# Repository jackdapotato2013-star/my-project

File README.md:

# my-project
A new project with 4 files

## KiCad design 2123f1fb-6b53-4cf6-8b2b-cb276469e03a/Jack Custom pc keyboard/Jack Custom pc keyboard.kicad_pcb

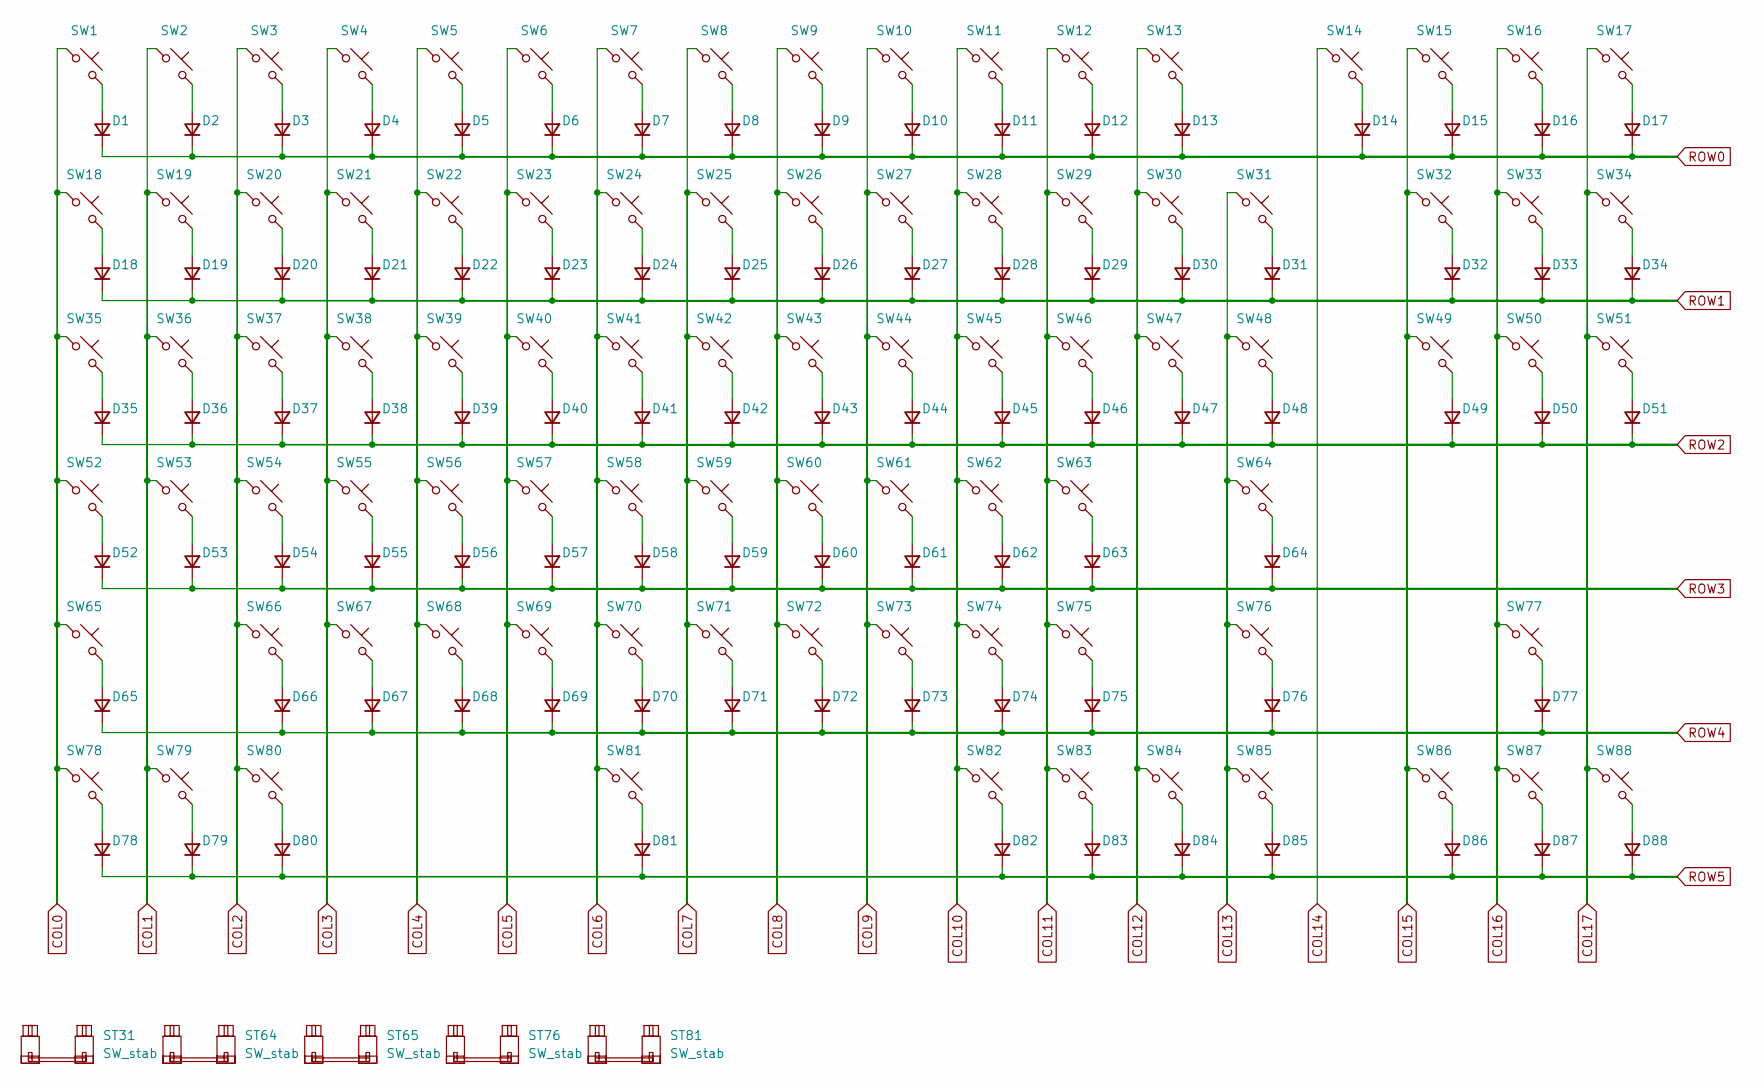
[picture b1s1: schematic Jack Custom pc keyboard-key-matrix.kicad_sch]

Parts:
D1, D2, D3, D4, D5, D6, D7, D8, D9, D10, D11, D12, D13, D14, D15, D16, D17, D18, D19, D20, D21, D22, D23, D24, D25, D26, D27, D28, D29, D30, D31, D32, D33, D34, D35, D36, D37, D38, D39, D40, D41, D42, D43, D44, D45, D46, D47, D48, D49, D50, D51, D52, D53, D54, D55, D56, D57, D58, D59, D60, D61, D62, D63, D64, D65, D66, D67, D68, D69, D70, D71, D72, D73, D74, D75, D76, D77, D78, D79, D80, D81, D82, D83, D84, D85, D86, D87, D88: D; D_SOD-323F
ST31, ST64, ST65, ST76: SW_stab; Stabilizer_Cherry_MX_2.00u
ST81: SW_stab; Stabilizer_Cherry_MX_6.25u
SW1, SW2, SW3, SW4, SW5, SW6, SW7, SW8, SW9, SW10, SW11, SW12, SW13, SW14, SW15, SW16, SW17, SW18, SW19, SW20, SW21, SW22, SW23, SW24, SW25, SW26, SW27, SW28, SW29, SW30, SW32, SW33, SW34, SW36, SW37, SW38, SW39, SW40, SW41, SW42, SW43, SW44, SW45, SW46, SW47, SW49, SW50, SW51, SW53, SW54, SW55, SW56, SW57, SW58, SW59, SW60, SW61, SW62, SW63, SW66, SW67, SW68, SW69, SW70, SW71, SW72, SW73, SW74, SW75, SW77, SW86, SW87, SW88: SW_Push; SW_Cherry_MX_PCB_1.00u
SW31: SW_Push; SW_Cherry_MX_PCB_2.00u
SW35, SW48: SW_Push; SW_Cherry_MX_PCB_1.50u
SW52: SW_Push; SW_Cherry_MX_PCB_1.75u
SW64, SW65: SW_Push; SW_Cherry_MX_PCB_2.25u
SW76: SW_Push; SW_Cherry_MX_PCB_2.75u
SW78, SW79, SW80, SW82, SW83, SW84, SW85: SW_Push; SW_Cherry_MX_PCB_1.25u
SW81: SW_Push; SW_Cherry_MX_PCB_6.25u

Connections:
COL0: SW1.1, SW18.1, SW35.1, SW52.1, SW65.1, SW78.1
COL1: SW2.1, SW19.1, SW36.1, SW53.1, SW79.1
COL2: SW3.1, SW20.1, SW37.1, SW54.1, SW66.1, SW80.1
COL3: SW4.1, SW21.1, SW38.1, SW55.1, SW67.1
COL4: SW5.1, SW22.1, SW39.1, SW56.1, SW68.1
COL5: SW6.1, SW23.1, SW40.1, SW57.1, SW69.1
COL6: SW7.1, SW24.1, SW41.1, SW58.1, SW70.1, SW81.1
COL7: SW8.1, SW25.1, SW42.1, SW59.1, SW71.1
COL8: SW9.1, SW26.1, SW43.1, SW60.1, SW72.1
COL9: SW10.1, SW27.1, SW44.1, SW61.1, SW73.1
COL10: SW11.1, SW28.1, SW45.1, SW62.1, SW74.1, SW82.1
COL11: SW12.1, SW29.1, SW46.1, SW63.1, SW75.1, SW83.1
COL12: SW13.1, SW30.1, SW47.1, SW84.1
COL13: SW31.1, SW48.1, SW64.1, SW76.1, SW85.1
COL14: SW14.1
COL15: SW15.1, SW32.1, SW49.1, SW86.1
COL16: SW16.1, SW33.1, SW50.1, SW77.1, SW87.1
COL17: SW17.1, SW34.1, SW51.1, SW88.1
unnamed: D1.2 (A), SW1.2
unnamed: D2.2 (A), SW2.2
unnamed: D3.2 (A), SW3.2
unnamed: D4.2 (A), SW4.2
unnamed: D5.2 (A), SW5.2
unnamed: D6.2 (A), SW6.2
unnamed: D7.2 (A), SW7.2
unnamed: D8.2 (A), SW8.2
unnamed: D9.2 (A), SW9.2
unnamed: D10.2 (A), SW10.2
unnamed: D11.2 (A), SW11.2
unnamed: D12.2 (A), SW12.2
unnamed: D13.2 (A), SW13.2
unnamed: D14.2 (A), SW14.2
unnamed: D15.2 (A), SW15.2
unnamed: D16.2 (A), SW16.2
unnamed: D17.2 (A), SW17.2
unnamed: D18.2 (A), SW18.2
unnamed: D19.2 (A), SW19.2
unnamed: D20.2 (A), SW20.2
unnamed: D21.2 (A), SW21.2
unnamed: D22.2 (A), SW22.2
unnamed: D23.2 (A), SW23.2
unnamed: D24.2 (A), SW24.2
unnamed: D25.2 (A), SW25.2
unnamed: D26.2 (A), SW26.2
unnamed: D27.2 (A), SW27.2
unnamed: D28.2 (A), SW28.2
unnamed: D29.2 (A), SW29.2
unnamed: D30.2 (A), SW30.2
unnamed: D31.2 (A), SW31.2
unnamed: D32.2 (A), SW32.2
unnamed: D33.2 (A), SW33.2
unnamed: D34.2 (A), SW34.2
unnamed: D35.2 (A), SW35.2
unnamed: D36.2 (A), SW36.2
unnamed: D37.2 (A), SW37.2
unnamed: D38.2 (A), SW38.2
unnamed: D39.2 (A), SW39.2
unnamed: D40.2 (A), SW40.2
unnamed: D41.2 (A), SW41.2
unnamed: D42.2 (A), SW42.2
unnamed: D43.2 (A), SW43.2
unnamed: D44.2 (A), SW44.2
unnamed: D45.2 (A), SW45.2
unnamed: D46.2 (A), SW46.2
unnamed: D47.2 (A), SW47.2
unnamed: D48.2 (A), SW48.2
unnamed: D49.2 (A), SW49.2
unnamed: D50.2 (A), SW50.2
unnamed: D51.2 (A), SW51.2
unnamed: D52.2 (A), SW52.2
unnamed: D53.2 (A), SW53.2
unnamed: D54.2 (A), SW54.2
unnamed: D55.2 (A), SW55.2
unnamed: D56.2 (A), SW56.2
unnamed: D57.2 (A), SW57.2
unnamed: D58.2 (A), SW58.2
unnamed: D59.2 (A), SW59.2
unnamed: D60.2 (A), SW60.2
unnamed: D61.2 (A), SW61.2
unnamed: D62.2 (A), SW62.2
unnamed: D63.2 (A), SW63.2
unnamed: D64.2 (A), SW64.2
unnamed: D65.2 (A), SW65.2
unnamed: D66.2 (A), SW66.2
unnamed: D67.2 (A), SW67.2
unnamed: D68.2 (A), SW68.2
unnamed: D69.2 (A), SW69.2
unnamed: D70.2 (A), SW70.2
unnamed: D71.2 (A), SW71.2
unnamed: D72.2 (A), SW72.2
unnamed: D73.2 (A), SW73.2
unnamed: D74.2 (A), SW74.2
unnamed: D75.2 (A), SW75.2
unnamed: D76.2 (A), SW76.2
unnamed: D77.2 (A), SW77.2
unnamed: D78.2 (A), SW78.2
unnamed: D79.2 (A), SW79.2
unnamed: D80.2 (A), SW80.2
unnamed: D81.2 (A), SW81.2
unnamed: D82.2 (A), SW82.2
unnamed: D83.2 (A), SW83.2
unnamed: D84.2 (A), SW84.2
unnamed: D85.2 (A), SW85.2
unnamed: D86.2 (A), SW86.2
unnamed: D87.2 (A), SW87.2
unnamed: D88.2 (A), SW88.2
ROW0: D1.1 (K), D2.1 (K), D3.1 (K), D4.1 (K), D5.1 (K), D6.1 (K), D7.1 (K), D8.1 (K), D9.1 (K), D10.1 (K), D11.1 (K), D12.1 (K), D13.1 (K), D14.1 (K), D15.1 (K), D16.1 (K), D17.1 (K)
ROW1: D18.1 (K), D19.1 (K), D20.1 (K), D21.1 (K), D22.1 (K), D23.1 (K), D24.1 (K), D25.1 (K), D26.1 (K), D27.1 (K), D28.1 (K), D29.1 (K), D30.1 (K), D31.1 (K), D32.1 (K), D33.1 (K), D34.1 (K)
ROW2: D35.1 (K), D36.1 (K), D37.1 (K), D38.1 (K), D39.1 (K), D40.1 (K), D41.1 (K), D42.1 (K), D43.1 (K), D44.1 (K), D45.1 (K), D46.1 (K), D47.1 (K), D48.1 (K), D49.1 (K), D50.1 (K), D51.1 (K)
ROW3: D52.1 (K), D53.1 (K), D54.1 (K), D55.1 (K), D56.1 (K), D57.1 (K), D58.1 (K), D59.1 (K), D60.1 (K), D61.1 (K), D62.1 (K), D63.1 (K), D64.1 (K)
ROW4: D65.1 (K), D66.1 (K), D67.1 (K), D68.1 (K), D69.1 (K), D70.1 (K), D71.1 (K), D72.1 (K), D73.1 (K), D74.1 (K), D75.1 (K), D76.1 (K), D77.1 (K)
ROW5: D78.1 (K), D79.1 (K), D80.1 (K), D81.1 (K), D82.1 (K), D83.1 (K), D84.1 (K), D85.1 (K), D86.1 (K), D87.1 (K), D88.1 (K)

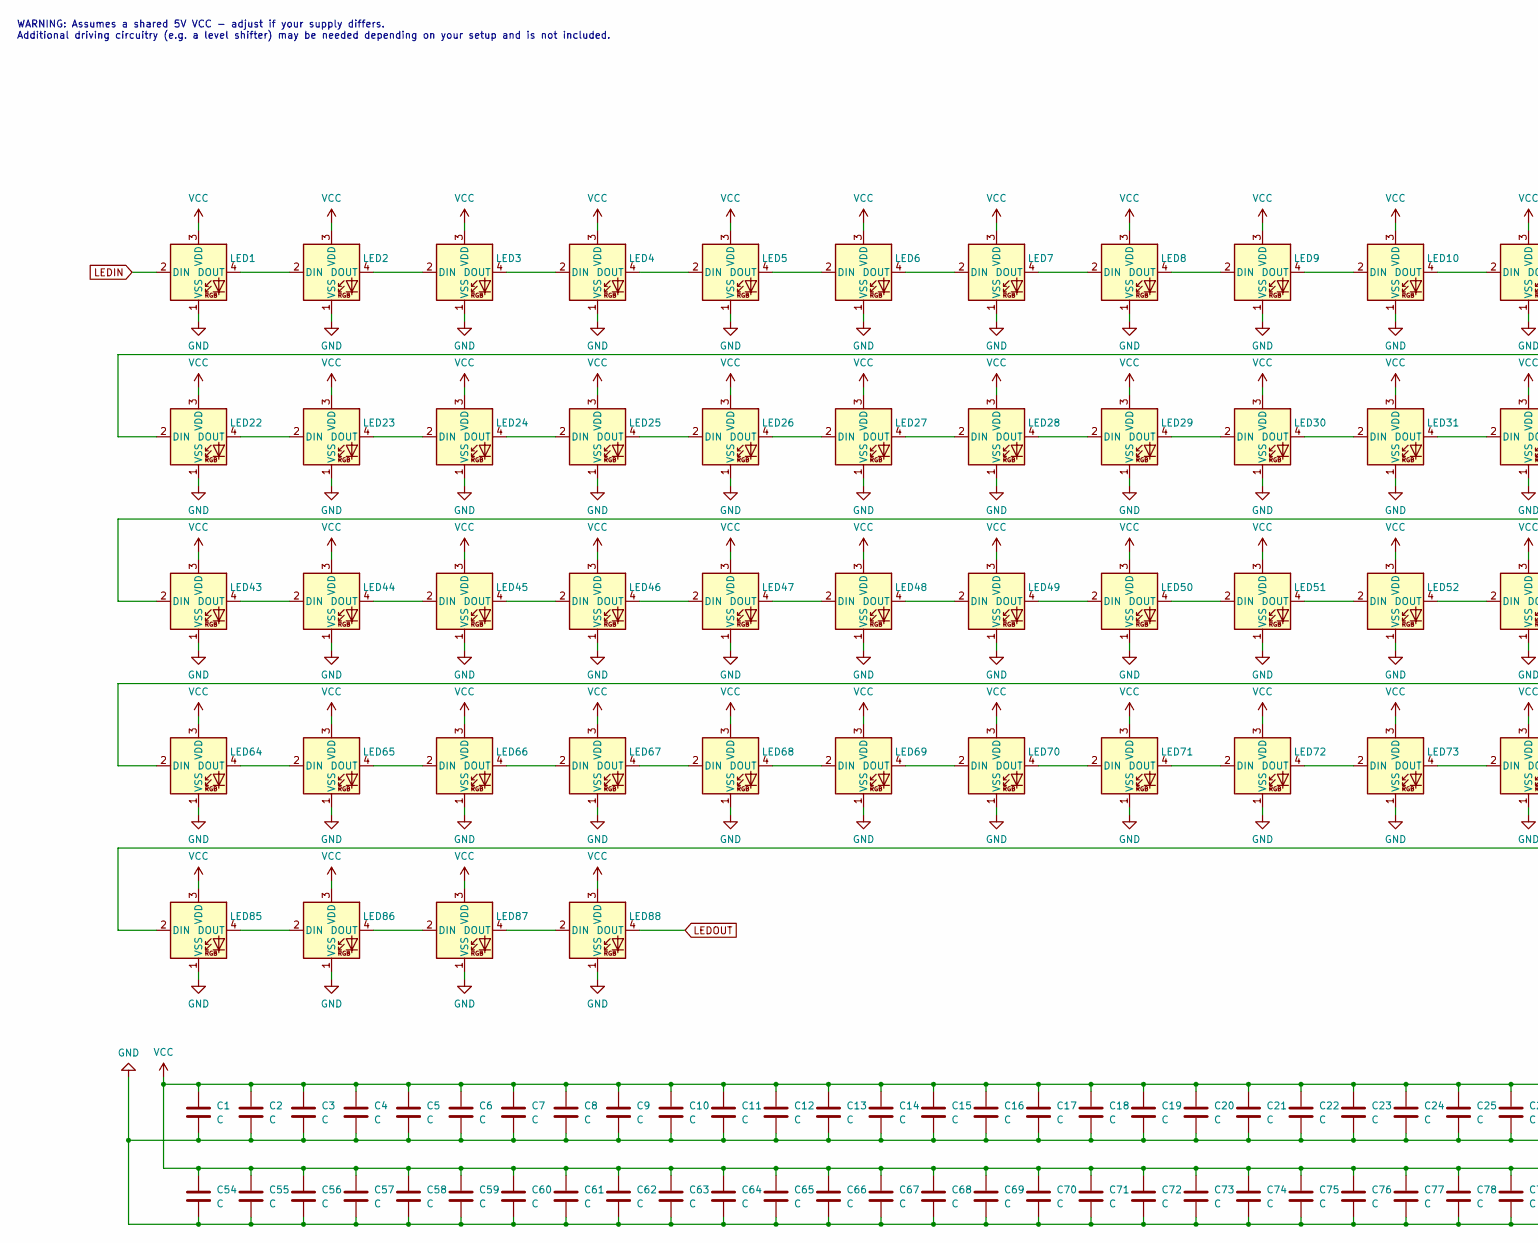
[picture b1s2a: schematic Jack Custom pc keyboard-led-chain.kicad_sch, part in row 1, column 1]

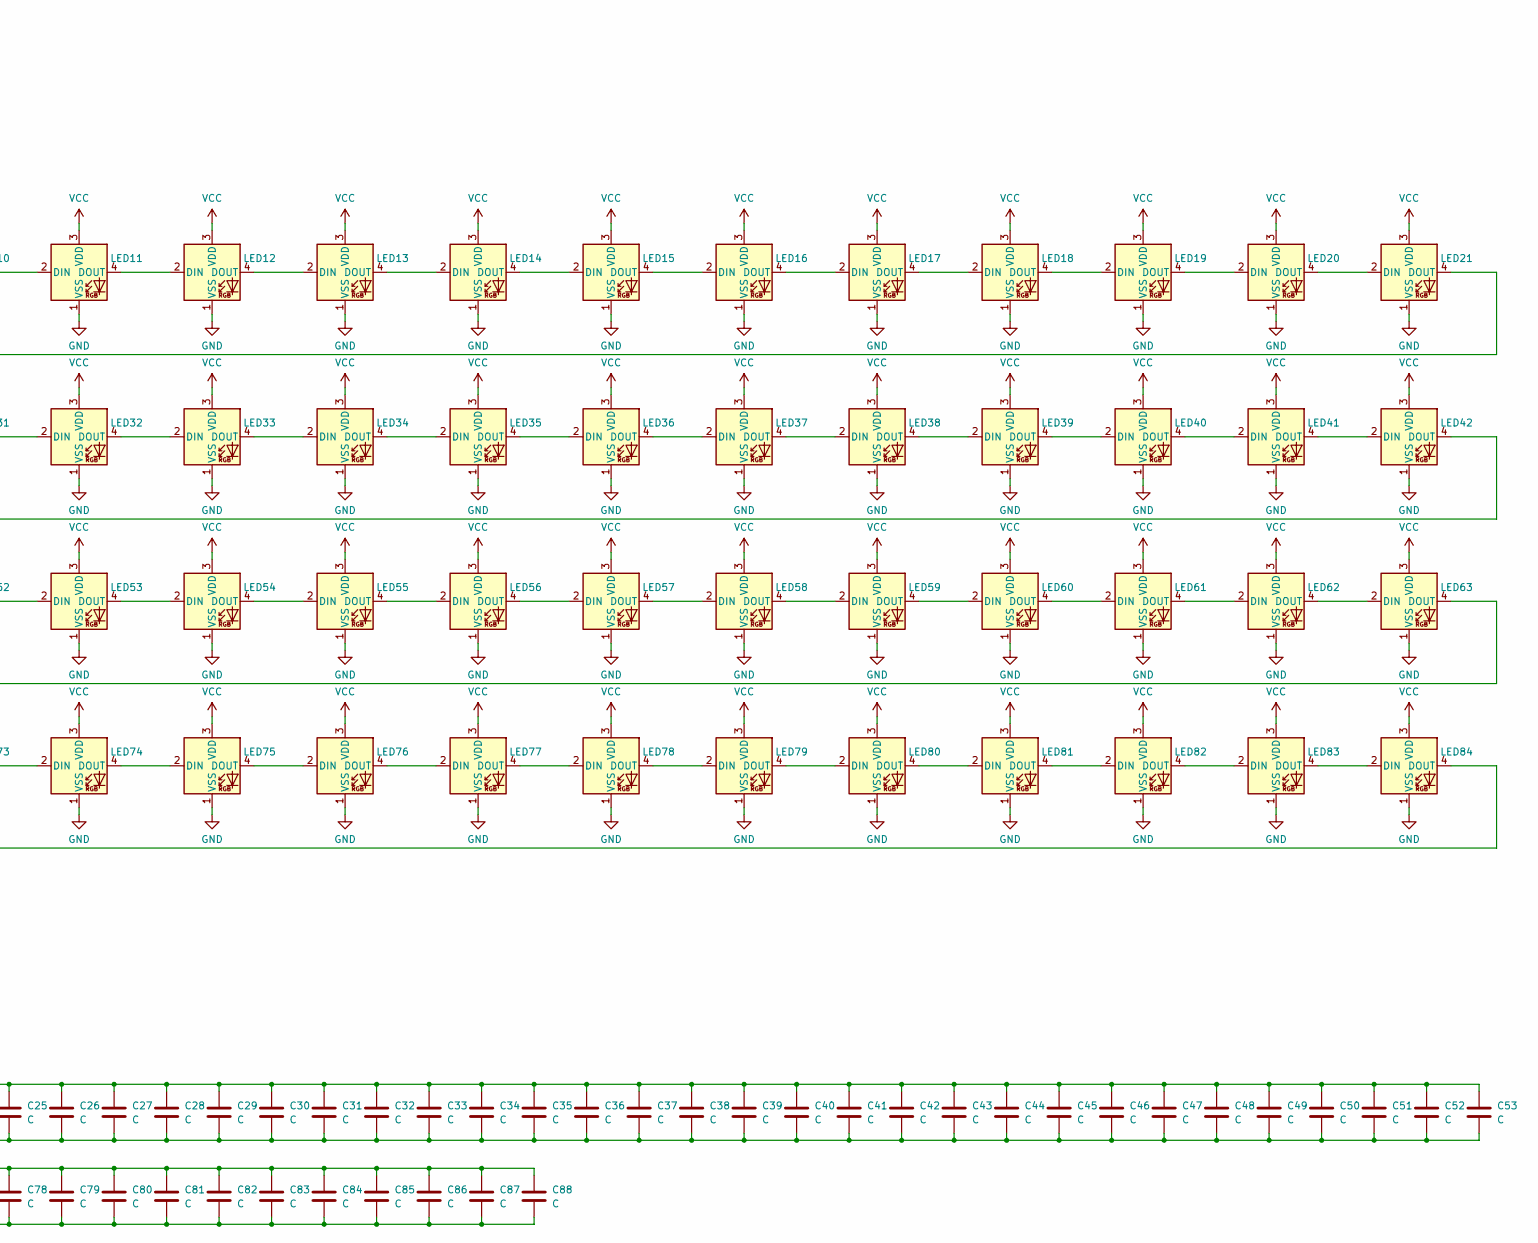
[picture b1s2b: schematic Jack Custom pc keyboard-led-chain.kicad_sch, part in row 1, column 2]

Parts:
C1, C2, C3, C4, C5, C6, C7, C8, C9, C10, C11, C12, C13, C14, C15, C16, C17, C18, C19, C20, C21, C22, C23, C24, C25, C26, C27, C28, C29, C30, C31, C32, C33, C34, C35, C36, C37, C38, C39, C40, C41, C42, C43, C44, C45, C46, C47, C48, C49, C50, C51, C52, C53, C54, C55, C56, C57, C58, C59, C60, C61, C62, C63, C64, C65, C66, C67, C68, C69, C70, C71, C72, C73, C74, C75, C76, C77, C78, C79, C80, C81, C82, C83, C84, C85, C86, C87, C88: C; C_0402_1005Metric
LED1, LED2, LED3, LED4, LED5, LED6, LED7, LED8, LED9, LED10, LED11, LED12, LED13, LED14, LED15, LED16, LED17, LED18, LED19, LED20, LED21, LED22, LED23, LED24, LED25, LED26, LED27, LED28, LED29, LED30, LED31, LED32, LED33, LED34, LED35, LED36, LED37, LED38, LED39, LED40, LED41, LED42, LED43, LED44, LED45, LED46, LED47, LED48, LED49, LED50, LED51, LED52, LED53, LED54, LED55, LED56, LED57, LED58, LED59, LED60, LED61, LED62, LED63, LED64, LED65, LED66, LED67, LED68, LED69, LED70, LED71, LED72, LED73, LED74, LED75, LED76, LED77, LED78, LED79, LED80, LED81, LED82, LED83, LED84, LED85, LED86, LED87, LED88: SK6812MINI-E; LED_SK6812MINI-E_3.2x2.8mm_P1.5mm_ReverseMount

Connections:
GND: C1.2, C2.2, C3.2, C4.2, C5.2, C6.2, C7.2, C8.2, C9.2, C10.2, C11.2, C12.2, C13.2, C14.2, C15.2, C16.2, C17.2, C18.2, C19.2, C20.2, C21.2, C22.2, C23.2, C24.2, C25.2, C26.2, C27.2, C28.2, C29.2, C30.2, C31.2, C32.2, C33.2, C34.2, C35.2, C36.2, C37.2, C38.2, C39.2, C40.2, C41.2, C42.2, C43.2, C44.2, C45.2, C46.2, C47.2, C48.2, C49.2, C50.2, C51.2, C52.2, C53.2, C54.2, C55.2, C56.2, C57.2, C58.2, C59.2, C60.2, C61.2, C62.2, C63.2, C64.2, C65.2, C66.2, C67.2, C68.2, C69.2, C70.2, C71.2, C72.2, C73.2, C74.2, C75.2, C76.2, C77.2, C78.2, C79.2, C80.2, C81.2, C82.2, C83.2, C84.2, C85.2, C86.2, C87.2, C88.2, LED1.1 (VSS), LED2.1 (VSS), LED3.1 (VSS), LED4.1 (VSS), LED5.1 (VSS), LED6.1 (VSS), LED7.1 (VSS), LED8.1 (VSS), LED9.1 (VSS), LED10.1 (VSS), LED11.1 (VSS), LED12.1 (VSS), LED13.1 (VSS), LED14.1 (VSS), LED15.1 (VSS), LED16.1 (VSS), LED17.1 (VSS), LED18.1 (VSS), LED19.1 (VSS), LED20.1 (VSS), LED21.1 (VSS), LED22.1 (VSS), LED23.1 (VSS), LED24.1 (VSS), LED25.1 (VSS), LED26.1 (VSS), LED27.1 (VSS), LED28.1 (VSS), LED29.1 (VSS), LED30.1 (VSS), LED31.1 (VSS), LED32.1 (VSS), LED33.1 (VSS), LED34.1 (VSS), LED35.1 (VSS), LED36.1 (VSS), LED37.1 (VSS), LED38.1 (VSS), LED39.1 (VSS), LED40.1 (VSS), LED41.1 (VSS), LED42.1 (VSS), LED43.1 (VSS), LED44.1 (VSS), LED45.1 (VSS), LED46.1 (VSS), LED47.1 (VSS), LED48.1 (VSS), LED49.1 (VSS), LED50.1 (VSS), LED51.1 (VSS), LED52.1 (VSS), LED53.1 (VSS), LED54.1 (VSS), LED55.1 (VSS), LED56.1 (VSS), LED57.1 (VSS), LED58.1 (VSS), LED59.1 (VSS), LED60.1 (VSS), LED61.1 (VSS), LED62.1 (VSS), LED63.1 (VSS), LED64.1 (VSS), LED65.1 (VSS), LED66.1 (VSS), LED67.1 (VSS), LED68.1 (VSS), LED69.1 (VSS), LED70.1 (VSS), LED71.1 (VSS), LED72.1 (VSS), LED73.1 (VSS), LED74.1 (VSS), LED75.1 (VSS), LED76.1 (VSS), LED77.1 (VSS), LED78.1 (VSS), LED79.1 (VSS), LED80.1 (VSS), LED81.1 (VSS), LED82.1 (VSS), LED83.1 (VSS), LED84.1 (VSS), LED85.1 (VSS), LED86.1 (VSS), LED87.1 (VSS), LED88.1 (VSS)
LEDIN: LED1.2 (DIN)
LEDOUT: LED88.4 (DOUT)
unnamed: LED1.4 (DOUT), LED2.2 (DIN)
unnamed: LED2.4 (DOUT), LED3.2 (DIN)
unnamed: LED3.4 (DOUT), LED4.2 (DIN)
unnamed: LED4.4 (DOUT), LED5.2 (DIN)
unnamed: LED5.4 (DOUT), LED6.2 (DIN)
unnamed: LED6.4 (DOUT), LED7.2 (DIN)
unnamed: LED7.4 (DOUT), LED8.2 (DIN)
unnamed: LED8.4 (DOUT), LED9.2 (DIN)
unnamed: LED9.4 (DOUT), LED10.2 (DIN)
unnamed: LED10.4 (DOUT), LED11.2 (DIN)
unnamed: LED11.4 (DOUT), LED12.2 (DIN)
unnamed: LED12.4 (DOUT), LED13.2 (DIN)
unnamed: LED13.4 (DOUT), LED14.2 (DIN)
unnamed: LED14.4 (DOUT), LED15.2 (DIN)
unnamed: LED15.4 (DOUT), LED16.2 (DIN)
unnamed: LED16.4 (DOUT), LED17.2 (DIN)
unnamed: LED17.4 (DOUT), LED18.2 (DIN)
unnamed: LED18.4 (DOUT), LED19.2 (DIN)
unnamed: LED19.4 (DOUT), LED20.2 (DIN)
unnamed: LED20.4 (DOUT), LED21.2 (DIN)
unnamed: LED21.4 (DOUT), LED22.2 (DIN)
unnamed: LED22.4 (DOUT), LED23.2 (DIN)
unnamed: LED23.4 (DOUT), LED24.2 (DIN)
unnamed: LED24.4 (DOUT), LED25.2 (DIN)
unnamed: LED25.4 (DOUT), LED26.2 (DIN)
unnamed: LED26.4 (DOUT), LED27.2 (DIN)
unnamed: LED27.4 (DOUT), LED28.2 (DIN)
unnamed: LED28.4 (DOUT), LED29.2 (DIN)
unnamed: LED29.4 (DOUT), LED30.2 (DIN)
unnamed: LED30.4 (DOUT), LED31.2 (DIN)
unnamed: LED31.4 (DOUT), LED32.2 (DIN)
unnamed: LED32.4 (DOUT), LED33.2 (DIN)
unnamed: LED33.4 (DOUT), LED34.2 (DIN)
unnamed: LED34.4 (DOUT), LED35.2 (DIN)
unnamed: LED35.4 (DOUT), LED36.2 (DIN)
unnamed: LED36.4 (DOUT), LED37.2 (DIN)
unnamed: LED37.4 (DOUT), LED38.2 (DIN)
unnamed: LED38.4 (DOUT), LED39.2 (DIN)
unnamed: LED39.4 (DOUT), LED40.2 (DIN)
unnamed: LED40.4 (DOUT), LED41.2 (DIN)
unnamed: LED41.4 (DOUT), LED42.2 (DIN)
unnamed: LED42.4 (DOUT), LED43.2 (DIN)
unnamed: LED43.4 (DOUT), LED44.2 (DIN)
unnamed: LED44.4 (DOUT), LED45.2 (DIN)
unnamed: LED45.4 (DOUT), LED46.2 (DIN)
unnamed: LED46.4 (DOUT), LED47.2 (DIN)
unnamed: LED47.4 (DOUT), LED48.2 (DIN)
unnamed: LED48.4 (DOUT), LED49.2 (DIN)
unnamed: LED49.4 (DOUT), LED50.2 (DIN)
unnamed: LED50.4 (DOUT), LED51.2 (DIN)
unnamed: LED51.4 (DOUT), LED52.2 (DIN)
unnamed: LED52.4 (DOUT), LED53.2 (DIN)
unnamed: LED53.4 (DOUT), LED54.2 (DIN)
unnamed: LED54.4 (DOUT), LED55.2 (DIN)
unnamed: LED55.4 (DOUT), LED56.2 (DIN)
unnamed: LED56.4 (DOUT), LED57.2 (DIN)
unnamed: LED57.4 (DOUT), LED58.2 (DIN)
unnamed: LED58.4 (DOUT), LED59.2 (DIN)
unnamed: LED59.4 (DOUT), LED60.2 (DIN)
unnamed: LED60.4 (DOUT), LED61.2 (DIN)
unnamed: LED61.4 (DOUT), LED62.2 (DIN)
unnamed: LED62.4 (DOUT), LED63.2 (DIN)
unnamed: LED63.4 (DOUT), LED64.2 (DIN)
unnamed: LED64.4 (DOUT), LED65.2 (DIN)
unnamed: LED65.4 (DOUT), LED66.2 (DIN)
unnamed: LED66.4 (DOUT), LED67.2 (DIN)
unnamed: LED67.4 (DOUT), LED68.2 (DIN)
unnamed: LED68.4 (DOUT), LED69.2 (DIN)
unnamed: LED69.4 (DOUT), LED70.2 (DIN)
unnamed: LED70.4 (DOUT), LED71.2 (DIN)
unnamed: LED71.4 (DOUT), LED72.2 (DIN)
unnamed: LED72.4 (DOUT), LED73.2 (DIN)
unnamed: LED73.4 (DOUT), LED74.2 (DIN)
unnamed: LED74.4 (DOUT), LED75.2 (DIN)
unnamed: LED75.4 (DOUT), LED76.2 (DIN)
unnamed: LED76.4 (DOUT), LED77.2 (DIN)
unnamed: LED77.4 (DOUT), LED78.2 (DIN)
unnamed: LED78.4 (DOUT), LED79.2 (DIN)
unnamed: LED79.4 (DOUT), LED80.2 (DIN)
unnamed: LED80.4 (DOUT), LED81.2 (DIN)
unnamed: LED81.4 (DOUT), LED82.2 (DIN)
unnamed: LED82.4 (DOUT), LED83.2 (DIN)
unnamed: LED83.4 (DOUT), LED84.2 (DIN)
unnamed: LED84.4 (DOUT), LED85.2 (DIN)
unnamed: LED85.4 (DOUT), LED86.2 (DIN)
unnamed: LED86.4 (DOUT), LED87.2 (DIN)
unnamed: LED87.4 (DOUT), LED88.2 (DIN)
VCC: C1.1, C2.1, C3.1, C4.1, C5.1, C6.1, C7.1, C8.1, C9.1, C10.1, C11.1, C12.1, C13.1, C14.1, C15.1, C16.1, C17.1, C18.1, C19.1, C20.1, C21.1, C22.1, C23.1, C24.1, C25.1, C26.1, C27.1, C28.1, C29.1, C30.1, C31.1, C32.1, C33.1, C34.1, C35.1, C36.1, C37.1, C38.1, C39.1, C40.1, C41.1, C42.1, C43.1, C44.1, C45.1, C46.1, C47.1, C48.1, C49.1, C50.1, C51.1, C52.1, C53.1, C54.1, C55.1, C56.1, C57.1, C58.1, C59.1, C60.1, C61.1, C62.1, C63.1, C64.1, C65.1, C66.1, C67.1, C68.1, C69.1, C70.1, C71.1, C72.1, C73.1, C74.1, C75.1, C76.1, C77.1, C78.1, C79.1, C80.1, C81.1, C82.1, C83.1, C84.1, C85.1, C86.1, C87.1, C88.1, LED1.3 (VDD), LED2.3 (VDD), LED3.3 (VDD), LED4.3 (VDD), LED5.3 (VDD), LED6.3 (VDD), LED7.3 (VDD), LED8.3 (VDD), LED9.3 (VDD), LED10.3 (VDD), LED11.3 (VDD), LED12.3 (VDD), LED13.3 (VDD), LED14.3 (VDD), LED15.3 (VDD), LED16.3 (VDD), LED17.3 (VDD), LED18.3 (VDD), LED19.3 (VDD), LED20.3 (VDD), LED21.3 (VDD), LED22.3 (VDD), LED23.3 (VDD), LED24.3 (VDD), LED25.3 (VDD), LED26.3 (VDD), LED27.3 (VDD), LED28.3 (VDD), LED29.3 (VDD), LED30.3 (VDD), LED31.3 (VDD), LED32.3 (VDD), LED33.3 (VDD), LED34.3 (VDD), LED35.3 (VDD), LED36.3 (VDD), LED37.3 (VDD), LED38.3 (VDD), LED39.3 (VDD), LED40.3 (VDD), LED41.3 (VDD), LED42.3 (VDD), LED43.3 (VDD), LED44.3 (VDD), LED45.3 (VDD), LED46.3 (VDD), LED47.3 (VDD), LED48.3 (VDD), LED49.3 (VDD), LED50.3 (VDD), LED51.3 (VDD), LED52.3 (VDD), LED53.3 (VDD), LED54.3 (VDD), LED55.3 (VDD), LED56.3 (VDD), LED57.3 (VDD), LED58.3 (VDD), LED59.3 (VDD), LED60.3 (VDD), LED61.3 (VDD), LED62.3 (VDD), LED63.3 (VDD), LED64.3 (VDD), LED65.3 (VDD), LED66.3 (VDD), LED67.3 (VDD), LED68.3 (VDD), LED69.3 (VDD), LED70.3 (VDD), LED71.3 (VDD), LED72.3 (VDD), LED73.3 (VDD), LED74.3 (VDD), LED75.3 (VDD), LED76.3 (VDD), LED77.3 (VDD), LED78.3 (VDD), LED79.3 (VDD), LED80.3 (VDD), LED81.3 (VDD), LED82.3 (VDD), LED83.3 (VDD), LED84.3 (VDD), LED85.3 (VDD), LED86.3 (VDD), LED87.3 (VDD), LED88.3 (VDD)

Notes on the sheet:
WARNING: Assumes a shared 5V VCC - adjust if your supply differs. Additional driving circuitry (e.g. a level shifter) may be needed depending on your setup and is not included.

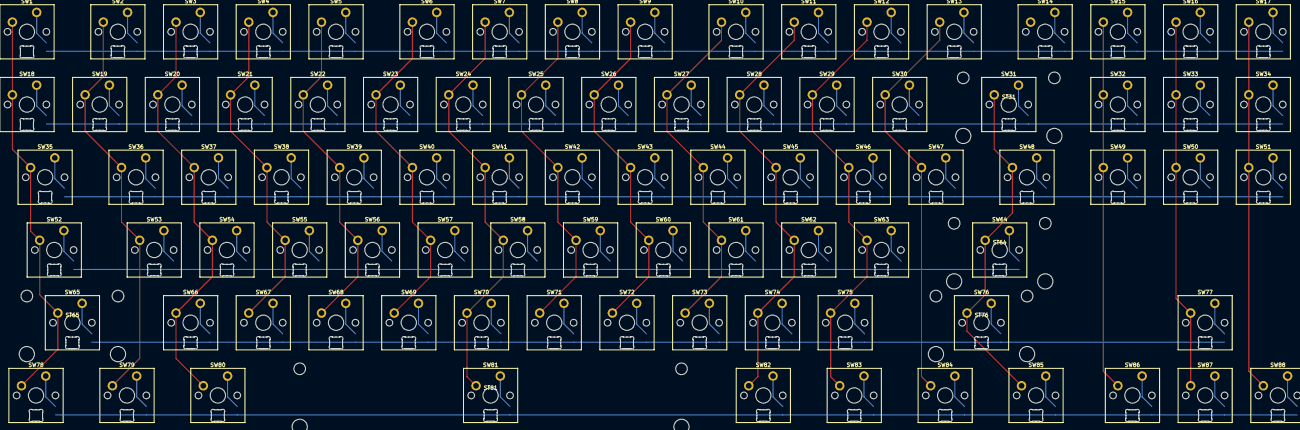
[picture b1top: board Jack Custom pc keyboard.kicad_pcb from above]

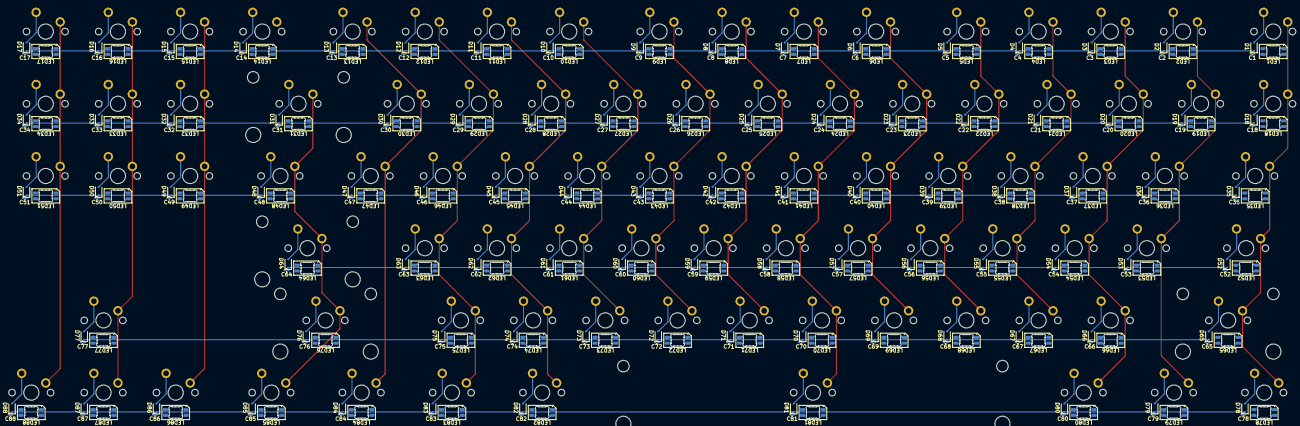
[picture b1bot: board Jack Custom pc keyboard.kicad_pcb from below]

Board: 2 copper layers, 357 parts (264 on the bottom side), 200 nets.
